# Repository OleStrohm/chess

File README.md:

# Chessboard

A chessboard made to play remotely with another person.

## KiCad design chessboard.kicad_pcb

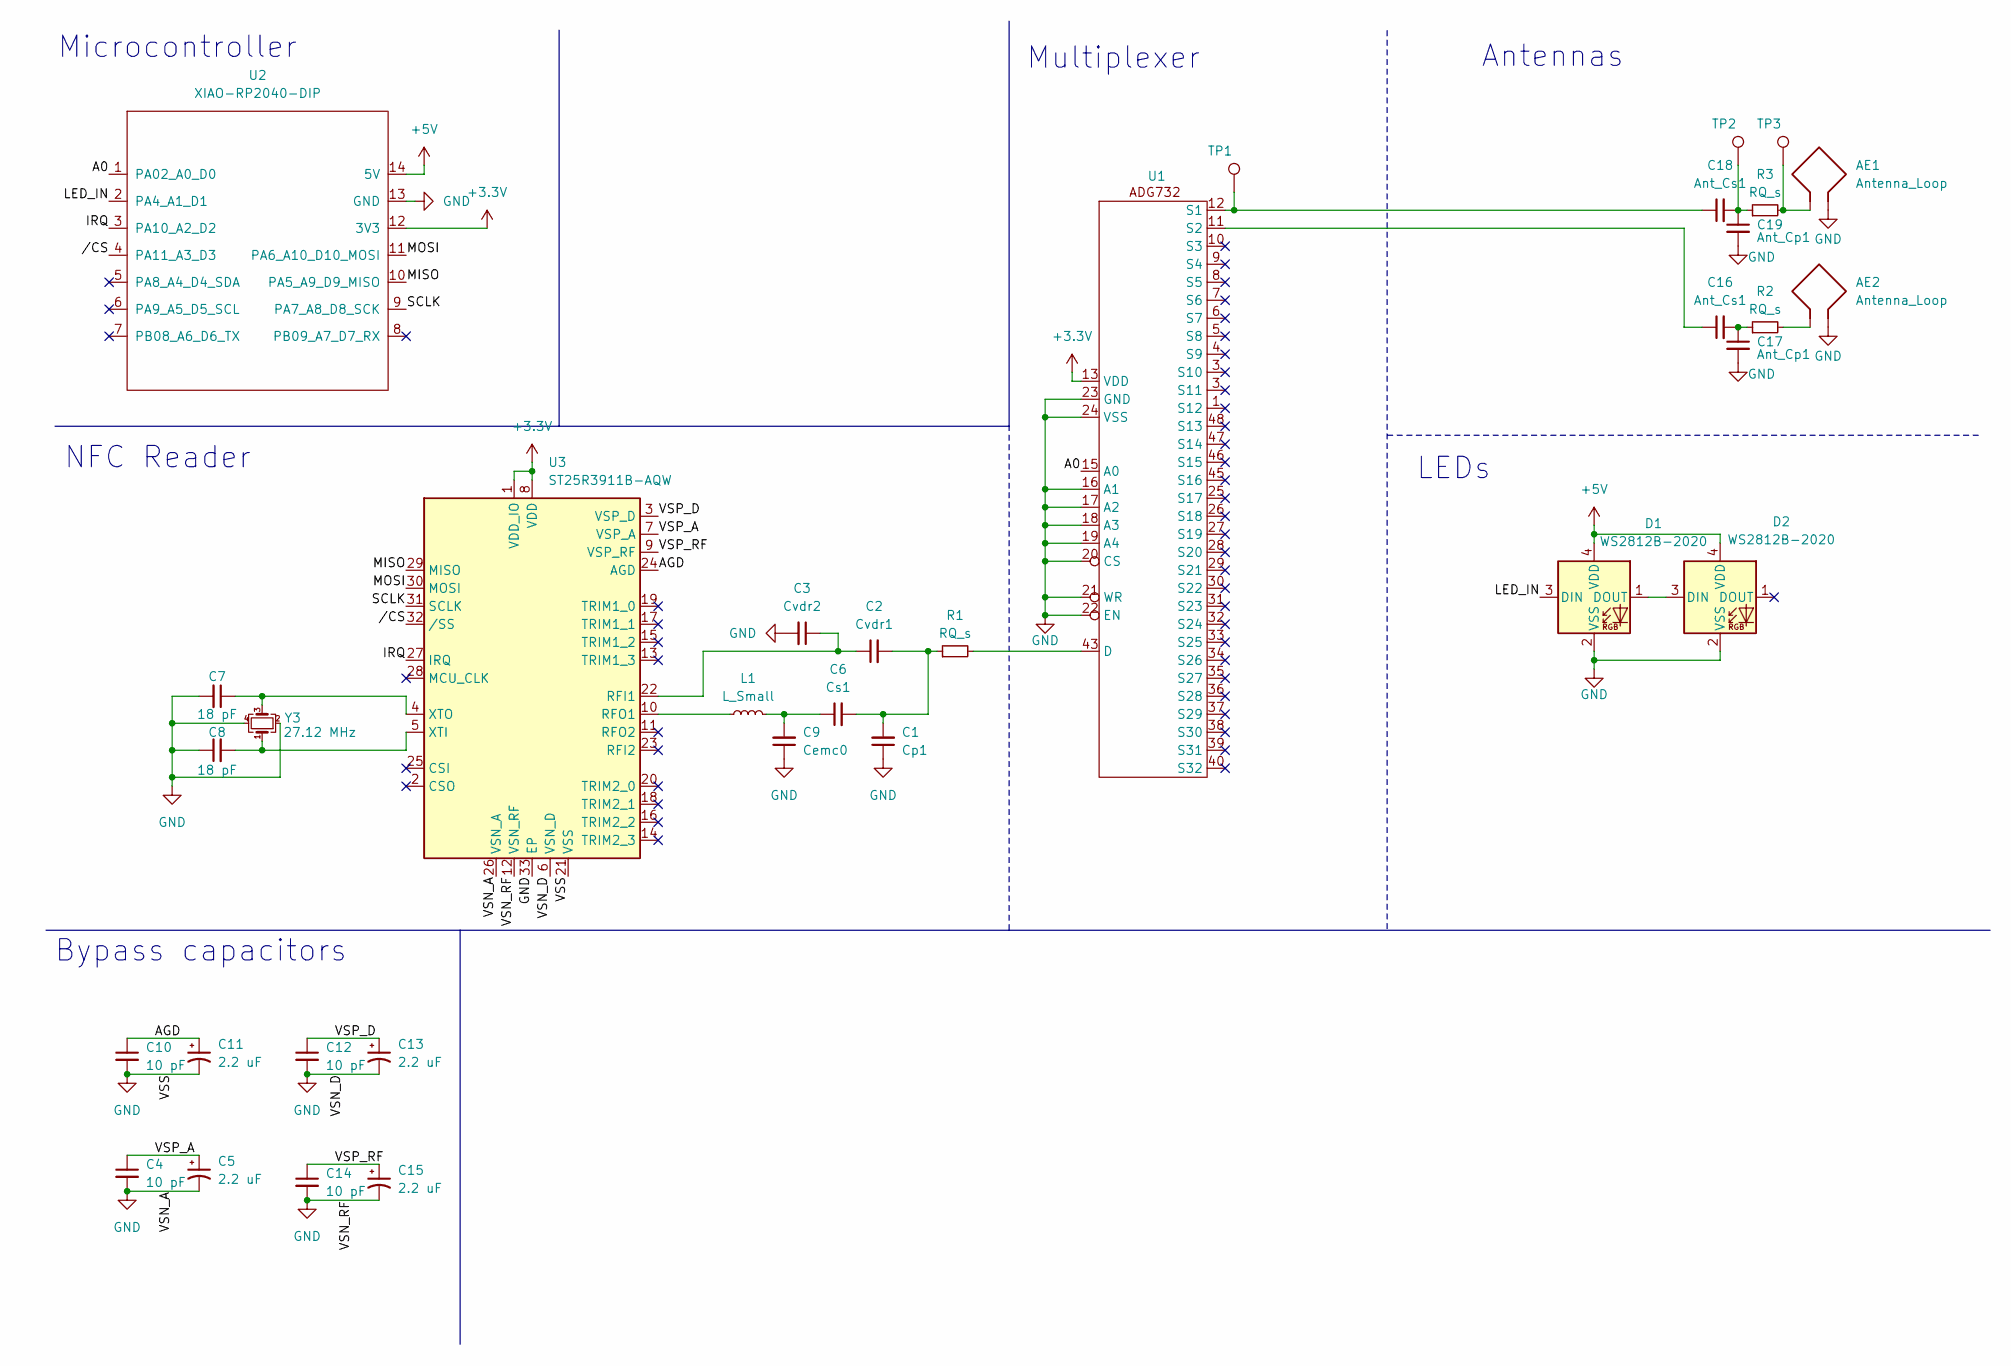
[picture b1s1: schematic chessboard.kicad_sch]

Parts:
AE1, AE2: Antenna_Loop; NFC_antenna
C1: Cp1; C_0805_2012Metric
C2: Cvdr1; C_0805_2012Metric
C3: Cvdr2; C_0805_2012Metric
C4, C10, C12, C14: 10 pF; C_0805_2012Metric
C5, C11, C13, C15: 2.2 uF; C_0805_2012Metric
C6: Cs1; C_0805_2012Metric
C7, C8: 18 pF; C_0805_2012Metric
C9: Cemc0; C_0805_2012Metric
C16, C18: Ant_Cs1; C_0805_2012Metric
C17, C19: Ant_Cp1; C_0805_2012Metric
D1, D2: WS2812B-2020; LED_WS2812B-2020_PLCC4_2.0x2.0mm
L1: L_Small; L_0805_2012Metric
R1, R2, R3: RQ_s; R_0805_2012Metric
TP1, TP2, TP3: TestPoint; TestPoint_Pad_D1.0mm
U1: TQFP-48_7x7mm_P0.5mm
U2: XIAO-RP2040-DIP; XIAO-RP2040-SMD
U3: ST25R3911B-AQW; VQFN-32-1EP_5x5mm_P0.5mm_EP3.5x3.5mm_ThermalVias
Y3: 27.12 MHz; Crystal_SMD_3225-4Pin_3.2x2.5mm

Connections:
+3.3V: U1.13 (VDD), U1.14 (VDD), U2.12 (3V3), U3.1 (VDD_IO), U3.8 (VDD)
+5V: D1.4 (VDD), D2.4 (VDD), U2.14 (5V)
/A0: U1.15 (A0), U2.1 (PA02_A0_D0)
/AGD: C10.1, C11.1, U3.24 (AGD)
/IRQ: U2.3 (PA10_A2_D2), U3.27 (IRQ)
/LED_IN: D1.3 (DIN), U2.2 (PA4_A1_D1)
/MISO: U2.10 (PA5_A9_D9_MISO), U3.29 (MISO)
/MOSI: U2.11 (PA6_A10_D10_MOSI), U3.30 (MOSI)
/SCLK: U2.9 (PA7_A8_D8_SCK), U3.31 (SCLK)
/VSP_A: C4.1, C5.1, U3.7 (VSP_A)
/VSP_D: C12.1, C13.1, U3.3 (VSP_D)
/VSP_RF: C14.1, C15.1, U3.9 (VSP_RF)
//CS: U2.4 (PA11_A3_D3), U3.32 (/SS)
GND: AE1.2, AE2.2, C1.1, C3.2, C4.2, C5.2, C7.2, C8.1, C9.1, C10.2, C11.2, C12.2, C13.2, C14.2, C15.2, C17.2, C19.2, D1.2 (VSS), D2.2 (VSS), U1.16 (A1), U1.17 (A2), U1.18 (A3), U1.19 (A4), U1.20 (CS), U1.21 (WR), U1.22 (EN), U1.23 (GND), U1.24 (VSS), U2.13 (GND), U3.6 (VSN_D), U3.12 (VSN_RF), U3.21 (VSS), U3.26 (VSN_A), U3.33 (EP), Y3.2, Y3.4
unnamed: AE1.1, R3.2, TP3.1
unnamed: AE2.1, R2.2
unnamed: C1.2, C2.2, C6.2, R1.1
unnamed: C6.1, C9.2, L1.2
unnamed: C16.2, C17.1, R2.1
unnamed: C18.2, C19.1, R3.1, TP2.1
unnamed: D1.1 (DOUT), D2.3 (DIN)
unnamed: R1.2, U1.43 (D)
unnamed: C18.1, TP1.1, U1.12 (S1)
unnamed: C16.1, U1.11 (S2)
unnamed: C2.1, C3.1, U3.22 (RFI1)
unnamed: L1.1, U3.10 (RFO1)
unnamed: C8.2, U3.5 (XTI), Y3.1
unnamed: C7.1, U3.4 (XTO), Y3.3

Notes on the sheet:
Multiplexer
Microcontroller
LEDs
Bypass capacitors
Antennas
NFC Reader

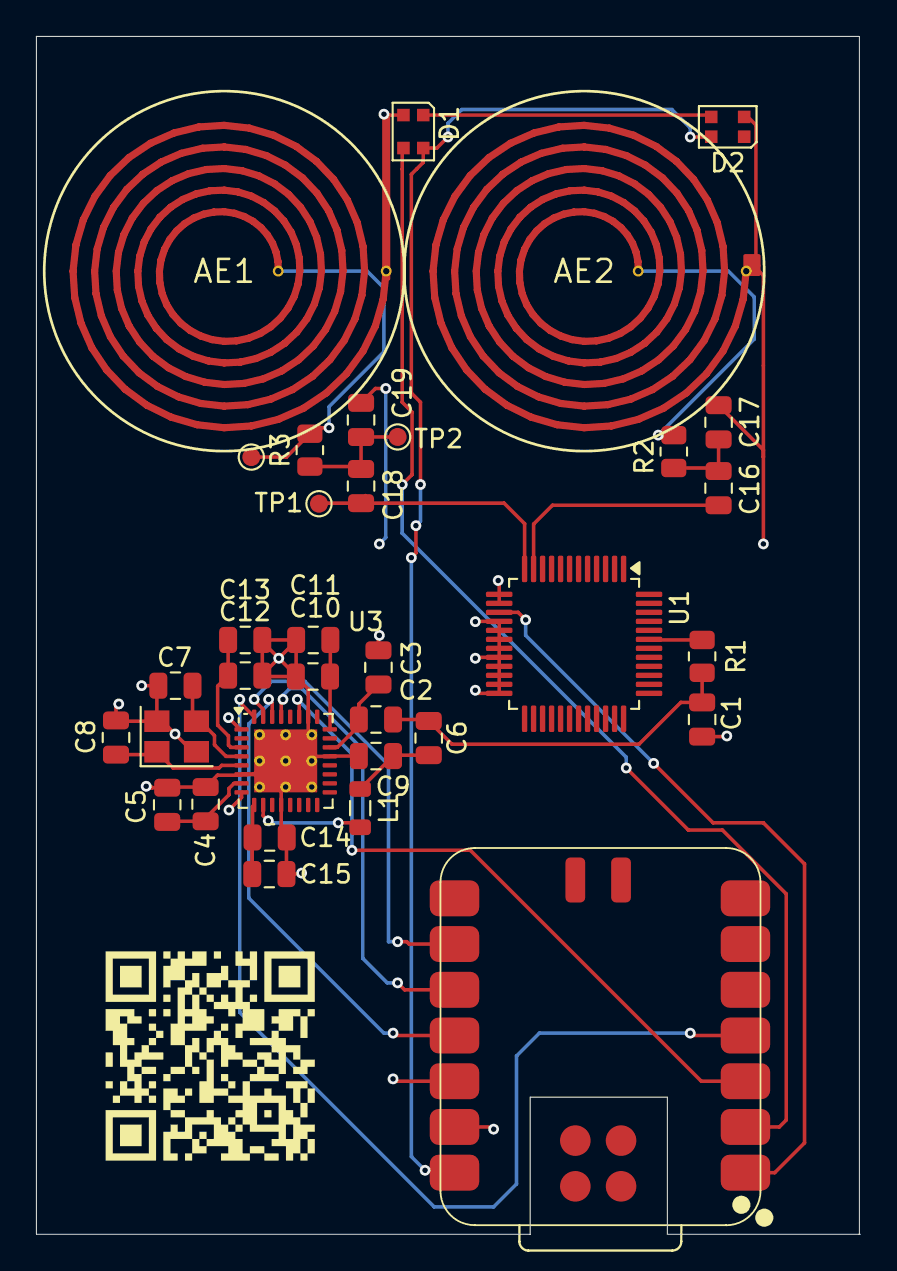
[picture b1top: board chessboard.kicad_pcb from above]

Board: 4 copper layers, 45.8 x 66.5 mm, 34 parts (0 on the bottom side), 28 nets.

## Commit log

2024-07-25 Added test macros
2024-07-25 Correctly named Rook and Knight
2024-07-25 Factored out tests
2025-07-28 Add QR code
2025-07-28 Create BOM
